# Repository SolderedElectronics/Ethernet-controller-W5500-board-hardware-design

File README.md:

# Ethernet controller W5500 board Hardware Design

## About the Product

|  |
| :----------------------------------------------------------: |
| [Buy Ethernet controller W5500 board](https://www.solde.red/333039) |

Designed with practicality in mind, this small yet powerful breakout contains the W5500 Ethernet controller, enabling fast and reliable internet connection for your Dasduino projects. Whether you’re an experienced enthusiast or just a beginner, this module is your reliable ally for connecting your Dasduino CORE to the internet.

In addition to the mentioned controller, the board features an RJ-45 connector for Ethernet cable connection, and the connection to Dasduino is via the SPI protocol.

So, whether you want to build a smart home automation system, create an IoT device with web connectivity, or simply explore the world of networked electronics with your Dasduino, the W5500 breakout is here. Say goodbye to connection problems and welcome the world of endless possibilities – all with the help of this little marvel!

---

## Repository Contents

This repository contains all design files for Ethernet controller W5500 board, organized as follows:

- **`CAD` folder**: Contains KiCAD design files, including:
  - Schematics
  - PCB layout
  - Panel PCB layout
  - Source 3D files in Fusion360, if any
  - All files are sorted by version with a detailed change log.
- **`OUTPUTS` folder**: Includes all production-ready files, such as:
  - Bill of Materials (BOM) and interactive BOM (iBOM)
  - PDF versions of schematics
  - 3D `.step` file of the board
  - 3D-printable models
  - Gerber files for PCB manufacturing
  - Image of the pinout of the board
  - Product image
  - Compliance, legal and generic sales documents

Refer to the `Change Log` in the CAD folder for details about updates between versions.

---

## Learn More About the Product

Beyond the repository, explore the following resources:

### Soldered Verify

The **Soldered Verify** system ensures every board you purchase from Soldered is fully functional. It also provides access to exclusive test data for your product. To get started, find the unique Soldered Verify ID on your product's packaging and enter the ID on the [Soldered Verify page](https://soldered.com/verify/) to access test results and additional product details.

### Soldered Community

Soldered Community is your go-to place for technical support. Our engineers track and answer all questions posted there, and it’s a great space for the maker community. Get answers to your questions and solutions for your challenges at [Soldered Community](https://soldered.com/community).

### solde.red

solde.red is an ultimate URL shortener and information hub. Access it by typing solde.red/ followed by your product SKU, e.g., [solde.red/333000](https://solde.red/333000), to find getting-started guides, datasheets, open-source hardware and software files, certifications, images, pinouts, and more. Read more about the shortener [here](https://solde.red/info/).

---

## Contributing

Contributions are welcome! Here’s how you can get involved:

- Submit pull requests to enhance the design or fix issues.
- Report bugs or problems by opening an issue.

We encourage community collaboration to make this product even better.

---

## About Soldered

[Soldered for Makers](https://soldered.com) specializes in designing and manufacturing electronic products tailored for enthusiasts, ranging from hobbyists to professionals. Our portfolio includes electronic boards, sensors, and actuators that are widely utilized in fields such as microelectronics, mechatronics, robotics, programming, and IoT. Every product we offer is designed in-house and built upon open-source hardware and software platforms. Proudly certified and manufactured within the European Union, our catalog likely includes the product you need for your project.

We complement these products with comprehensive tutorials and manuals, product descriptions, schematics, programming codes, and project examples. Our round-the-clock [customer and technical support](https://soldered.com/community) is available for all our products, irrespective of the sales channel. Soldered’s success and services reflect our maker community’s unwavering [trust](https://www.trustpilot.com/review/soldered.com), for which we are deeply grateful. Join our community and create using Soldered products.

---

## License

All Soldered open-source hardware (OSH) is under The TAPR Open Hardware License. Read more in the LICENSE file located in this repository.

**Disclaimer:**

No warranty - all designs in this repository are distributed in the hope that they will be useful, but without any warranty. They are provided "AS IS", therefore without warranty of any kind, either expressed or implied. The entire quality and performance of what you do with the contents of this repository are your responsibility. In no event Soldered Electronics will be liable for your damages, or losses, including any general, special, incidental, or consequential damage arising out of the use or inability to use the contents of this repository. 

---

## Have fun!

Thank you for your support from your fellow makers at Soldered Electronics.

Happy Making!

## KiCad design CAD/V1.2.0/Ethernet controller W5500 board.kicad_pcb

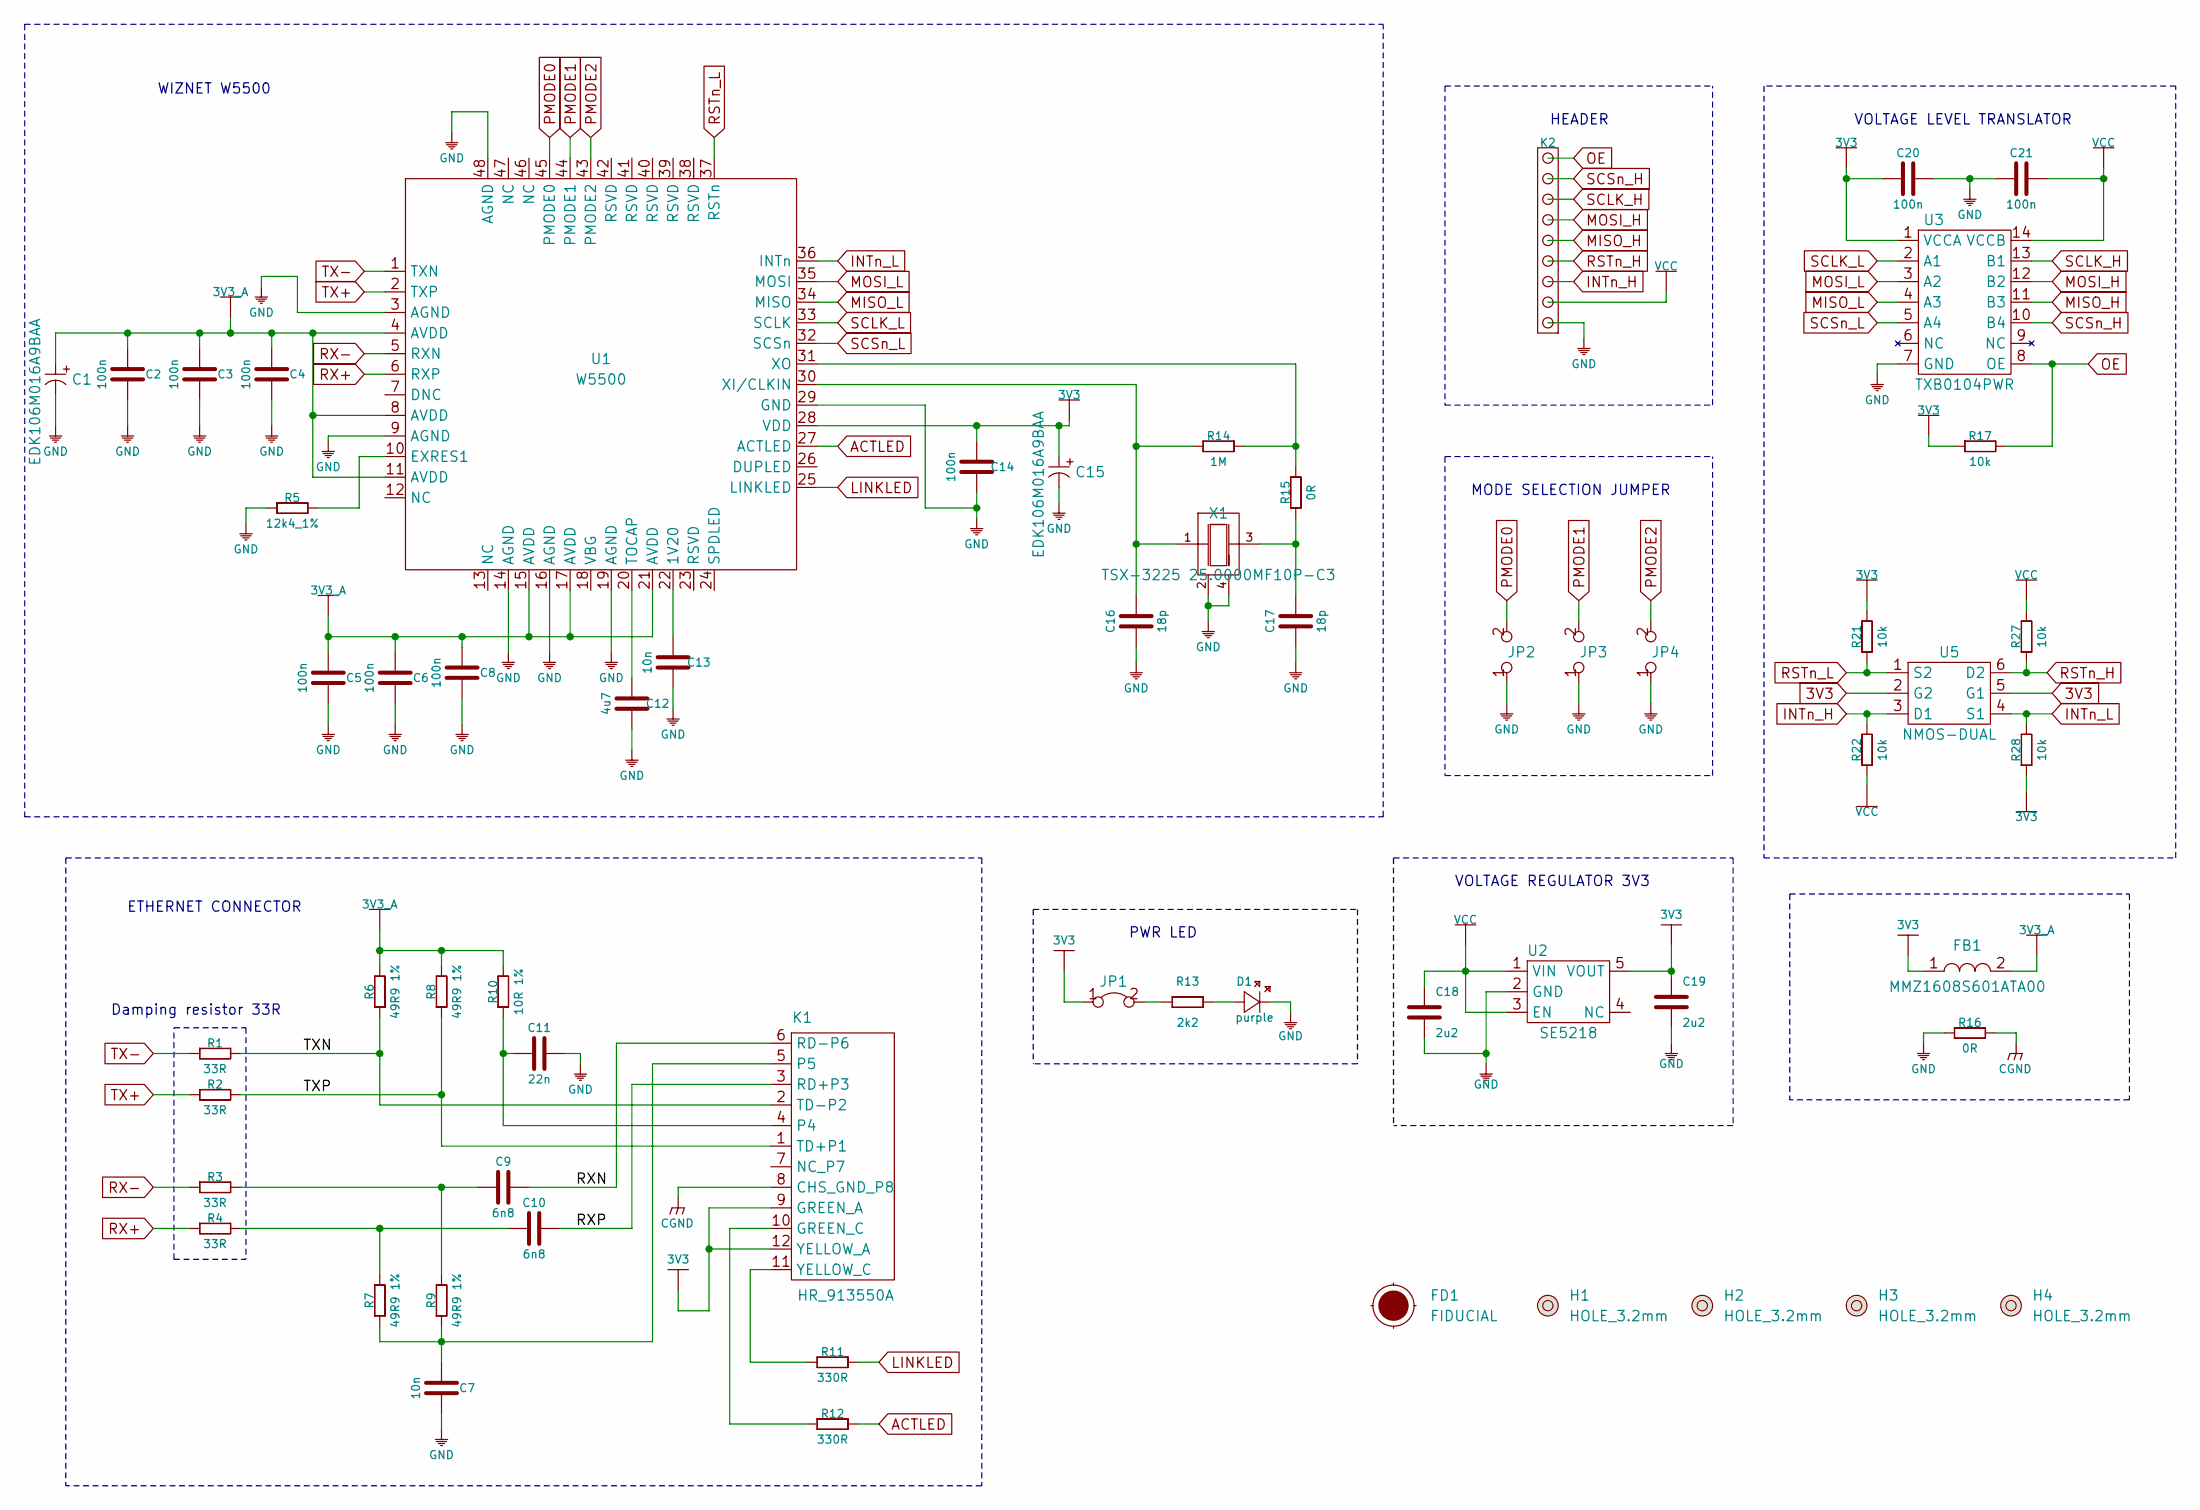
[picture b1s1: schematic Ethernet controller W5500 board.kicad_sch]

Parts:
C1, C15: EDK106M016A9BAA; ELECTROLITIC_CAP_4mm
C2, C3, C4, C5, C6, C8, C14, C20, C21: 100n; 0603C
C7, C13: 10n; 0603C
C9, C10: 6n8; 0603C
C11: 22n; 0603C
C12: 4u7; 0603C
C16, C17: 18p; 0603C
C18, C19: 2u2; 0603C
D1: purple; 0402LED
FB1: MMZ1608S601ATA00; 0603L
FD1: FIDUCIAL; FIDUCIAL_23
H1, H2, H3, H4: HOLE_3.2mm
JP1: SMD-JUMPER-CONNECTED_TRACE_SLODERMASK
JP2, JP3, JP4: SMD_JUMPER
K1: HR_913550A; HR913550A
K2: HEADER_MALE_9X1
R1, R2, R3, R4: 33R; 0603R
R5: 12k4_1%; 0603R
R6, R7, R8, R9: 49R9 1%; 0603R
R10: 10R 1%; 0603R
R11, R12: 330R; 0603R
R13: 2k2; 0402R
R14: 1M; 0603R
R15, R16: 0R; 0603R
R17, R21, R22, R27, R28: 10k; 0603R
U1: W5500; WIZnet W5500
U2: SE5218; SOT-23-5
U3: TXB0104PWR; TXB0104QPWRQ1
U5: NMOS-DUAL; SOT-363
X1: TSX-3225 25.0000MF10P-C3; CRYSTAL_3225__4_PAD

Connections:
3V3: C14.2, C15.1 (+), C19.2, C20.2, FB1.1, JP1.1, K1.9 (GREEN_A), K1.12 (YELLOW_A), R17.1, R21.2, R28.1, U1.28 (VDD), U2.5 (VOUT), U3.1 (VCCA), U5.2 (G2), U5.5 (G1)
3V3_A: C1.1 (+), C2.2, C3.2, C4.2, C5.2, C6.2, C8.2, FB1.2, R6.2, R8.2, R10.2, U1.4 (AVDD), U1.8 (AVDD), U1.11 (AVDD), U1.15 (AVDD), U1.17 (AVDD), U1.21 (AVDD)
/RXN: C9.1, K1.6 (RD-P6)
/RXP: C10.1, K1.3 (RD+P3)
/TXN: K1.2 (TD-P2), R1.2, R6.1
/TXP: K1.1 (TD+P1), R2.2, R8.1
ACTLED: R12.2, U1.27 (ACTLED)
CGND: K1.8 (CHS_GND_P8), R16.2
GND: C1.2 (-), C2.1, C3.1, C4.1, C5.1, C6.1, C7.1, C8.1, C11.1, C12.1, C13.1, C14.1, C15.2 (-), C16.1, C17.1, C18.1, C19.1, C20.1, C21.2, D1.2 (K), JP2.1, JP3.1, JP4.1, K2.1, R5.1, R16.1, U1.3 (AGND), U1.9 (AGND), U1.14 (AGND), U1.16 (AGND), U1.19 (AGND), U1.29 (GND), U1.48 (AGND), U2.2 (GND), U3.7 (GND), X1.2, X1.4
INTn_H: K2.3, R22.2, U5.3 (D1)
INTn_L: R28.2, U1.36 (INTn), U5.4 (S1)
LINKLED: R11.2, U1.25 (LINKLED)
MISO_H: K2.5, U3.11 (B3)
MISO_L: U1.34 (MISO), U3.4 (A3)
MOSI_H: K2.6, U3.12 (B2)
MOSI_L: U1.35 (MOSI), U3.3 (A2)
unnamed: C7.2, K1.5, R7.1, R9.1
unnamed: C9.2, R3.2, R9.2
unnamed: C10.2, R4.2, R7.2
unnamed: C11.2, K1.4, R10.1
unnamed: C12.2, U1.20 (TOCAP)
unnamed: C13.2, U1.22 (1V20)
unnamed: C16.2, R14.1, U1.30 (XI/CLKIN), X1.1
unnamed: C17.2, R15.1, X1.3
unnamed: D1.1 (A), R13.2
unnamed: JP1.2, R13.1
unnamed: K1.10 (GREEN_C), R12.1
unnamed: K1.11 (YELLOW_C), R11.1
unnamed: R5.2, U1.10 (EXRES1)
unnamed: R14.2, R15.2, U1.31 (XO)
OE: K2.9, R17.2, U3.8 (OE)
PMODE0: JP2.2, U1.45 (PMODE0)
PMODE1: JP3.2, U1.44 (PMODE1)
PMODE2: JP4.2, U1.43 (PMODE2)
RSTn_H: K2.4, R27.1, U5.6 (D2)
RSTn_L: R21.1, U1.37 (RSTn), U5.1 (S2)
RX+: R4.1, U1.6 (RXP)
RX-: R3.1, U1.5 (RXN)
SCLK_H: K2.7, U3.13 (B1)
SCLK_L: U1.33 (SCLK), U3.2 (A1)
SCSn_H: K2.8, U3.10 (B4)
SCSn_L: U1.32 (SCSn), U3.5 (A4)
TX+: R2.1, U1.2 (TXP)
TX-: R1.1, U1.1 (TXN)
VCC: C18.2, C21.1, K2.2, R22.1, R27.2, U2.1 (VIN), U2.3 (EN), U3.14 (VCCB)

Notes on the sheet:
WIZNET W5500
HEADER
PWR LED
Damping resistor 33R
ETHERNET CONNECTOR
VOLTAGE REGULATOR 3V3
MODE SELECTION JUMPER
VOLTAGE LEVEL TRANSLATOR

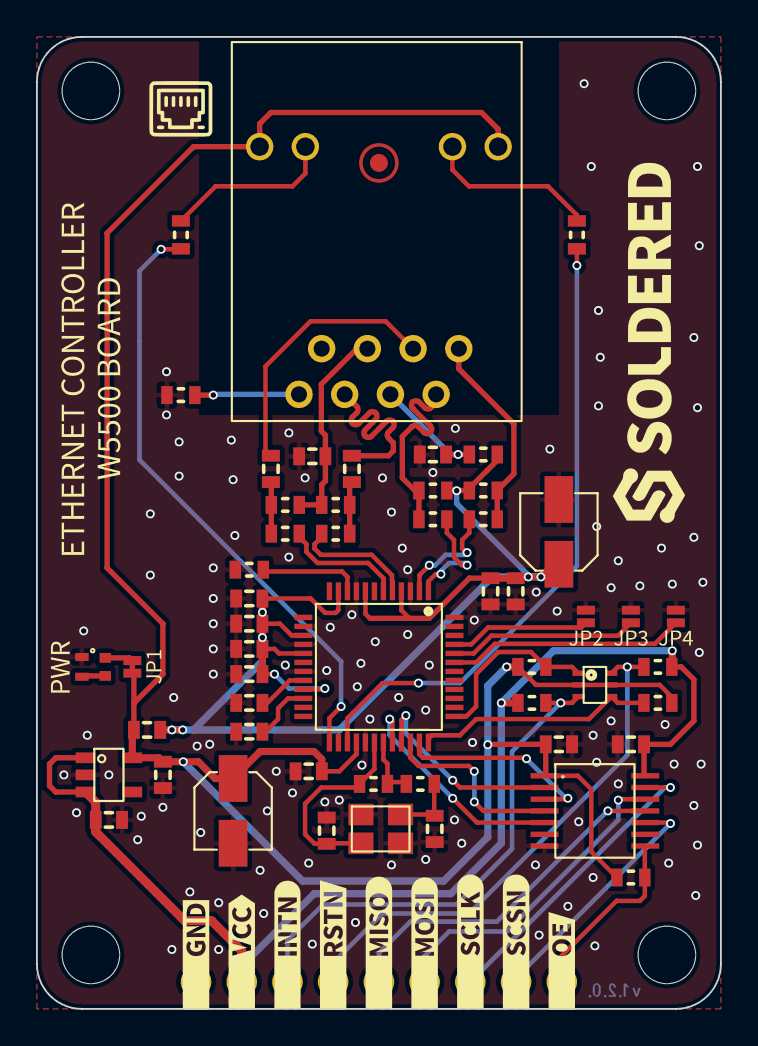
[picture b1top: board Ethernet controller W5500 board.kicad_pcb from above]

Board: 2 copper layers, 38.0 x 54.0 mm, 76 parts (0 on the bottom side), 45 nets.

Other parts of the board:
kibuzzard-6412C5EF: G***; kibuzzard-6412C5EF
kibuzzard-6412C6D5: G***; kibuzzard-6412C6D5
kibuzzard-6412C6F8: G***; kibuzzard-6412C6F8
kibuzzard-6412C7B1: G***; kibuzzard-6412C7B1
kibuzzard-6412C7D4: G***; kibuzzard-6412C7D4
kibuzzard-6412C7E6: G***; kibuzzard-6412C7E6
kibuzzard-6412C67E: G***; kibuzzard-6412C67E
kibuzzard-6412C73A: G***; kibuzzard-6412C73A
kibuzzard-6412C76F: G***; kibuzzard-6412C76F
kibuzzard-6412C79E: G***; kibuzzard-6412C79E
kibuzzard-6412C628: G***; kibuzzard-6412C628
kibuzzard-6412C635: G***; kibuzzard-6412C635
kibuzzard-6412C713: G***; kibuzzard-6412C713
kibuzzard-6412C763: G***; kibuzzard-6412C763
kibuzzard-6412C787: G***; kibuzzard-6412C787
kibuzzard-6412C805: G***; kibuzzard-6412C805

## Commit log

2022-08-06 Updating open source files.
